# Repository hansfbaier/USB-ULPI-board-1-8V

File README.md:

USB ULPI high speed PHY with 1.8V IO voltage
and Waveshare USB3300 board pinout
===

[![CC BY-SA 4.0][cc-by-sa-shield]][cc-by-sa]

This work is licensed under a [Creative Commons Attribution-NonCommercial-ShareAlike 4.0 International License][cc-by-sa].

[![CC BY-SA 4.0][cc-by-sa-image]][cc-by-sa]

[cc-by-sa]: http://creativecommons.org/licenses/by-nc-sa/4.0/
[cc-by-sa-image]: https://licensebuttons.net/l/by-nc-sa/4.0/88x31.png
[cc-by-sa-shield]: https://img.shields.io/badge/License-CC%20BY--NC--SA%204.0-lightgrey.svg

## Images

### JLCPCB

PCBs can be ordered fully-assembled (besides the pin header) from [JLCPCB](https://jlcpcb.com). Required files are
[PmodUsbUlpi_cpl_jlc.csv](PmodUsbUlpi_cpl_jlc.csv), [PmodUsbUlpi_bom_jlc.csv](PmodUsbUlpi_cpl_jlc.csv) and
[Gerber/PmodUsbUlpi.zip](Gerber/UsbUlpi.zip).

## Status
I am not sure the board works yet. I could not get it working on a couple of boards.
The 3.3V Version it is also very board dependent, on some boards it would work,
on others not, but I didn't test as many yet as with the 3.3V version.

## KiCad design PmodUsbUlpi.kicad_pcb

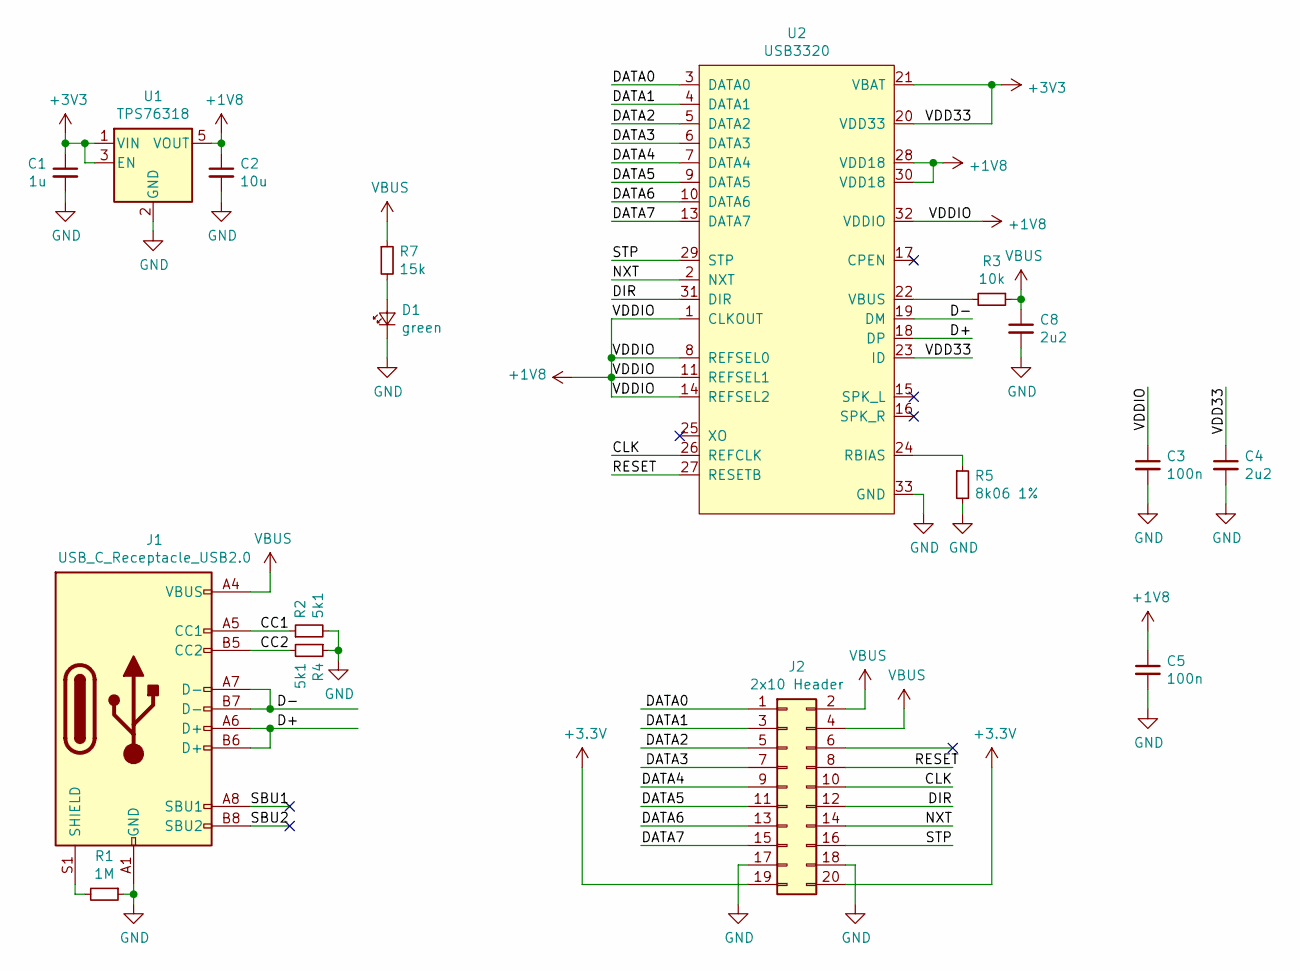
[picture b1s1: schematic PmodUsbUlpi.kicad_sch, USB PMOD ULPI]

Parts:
C1: 1u; C_0603_1608Metric; LCSC C15849
C2: 10u; C_0603_1608Metric; LCSC C19702
C3, C5: 100n; C_0603_1608Metric; LCSC C14663
C4, C8: 2u2; C_0603_1608Metric; LCSC C23630
D1: green; LED_0603_1608Metric; LCSC C72043
J1: USB_C_Receptacle_USB2.0; USB_C_Receptacle_XKB_U262-16XN-4BVC11; LCSC C165948
J2: 2x10 Header; PinHeader_2x10_P2.54mm_Horizontal
R1: 1M; R_0603_1608Metric; LCSC C22935
R2, R4: 5k1; R_0603_1608Metric; LCSC C23186
R3: 10k; R_0603_1608Metric; LCSC C25804
R5: 8k06 1%; R_0603_1608Metric; LCSC C23112
R7: 15k; R_0603_1608Metric; LCSC C22809
U1: TPS76318; SOT-23-5; LCSC C7099
U2: USB3320; QFN-32-1EP_5x5mm_P0.5mm_EP3.3x3.3mm; LCSC C132156

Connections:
+1V8: C2.1, C3.1, C5.1, U1.5 (VOUT), U2.1 (CLKOUT), U2.8 (REFSEL0), U2.11 (REFSEL1), U2.14 (REFSEL2), U2.28 (VDD18), U2.30 (VDD18), U2.32 (VDDIO)
/CC1: J1.A5 (CC1), R2.1
/CC2: J1.B5 (CC2), R4.2
/CLK: J2.10, U2.26 (REFCLK)
/D+: J1.A6 (D+), J1.B6 (D+), U2.18 (DP)
/D-: J1.A7 (D-), J1.B7 (D-), U2.19 (DM)
/DATA0: J2.1, U2.3 (DATA0)
/DATA1: J2.3, U2.4 (DATA1)
/DATA2: J2.5, U2.5 (DATA2)
/DATA3: J2.7, U2.6 (DATA3)
/DATA4: J2.9, U2.7 (DATA4)
/DATA5: J2.11, U2.9 (DATA5)
/DATA6: J2.13, U2.10 (DATA6)
/DATA7: J2.15, U2.13 (DATA7)
/DIR: J2.12, U2.31 (DIR)
/NXT: J2.14, U2.2 (NXT)
/RESET: J2.8, U2.27 (RESETB)
/SBU1: J1.A8 (SBU1)
/SBU2: J1.B8 (SBU2)
/STP: J2.16, U2.29 (STP)
GND: C1.2, C2.2, C3.2, C4.2, C5.2, C8.2, D1.1 (K), J1.A1 (GND), J1.A12 (GND), J1.B1 (GND), J1.B12 (GND), J2.17, J2.18, R1.1, R2.2, R4.1, R5.2, U1.2 (GND), U2.33 (GND)
unnamed: D1.2 (A), R7.2
unnamed: J1.S1 (SHIELD), R1.2
unnamed: R3.2, U2.22 (VBUS)
unnamed: R5.1, U2.24 (RBIAS)
VBUS: C8.1, J1.A4 (VBUS), J1.A9 (VBUS), J1.B4 (VBUS), J1.B9 (VBUS), J2.2, J2.4, R3.1, R7.1

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
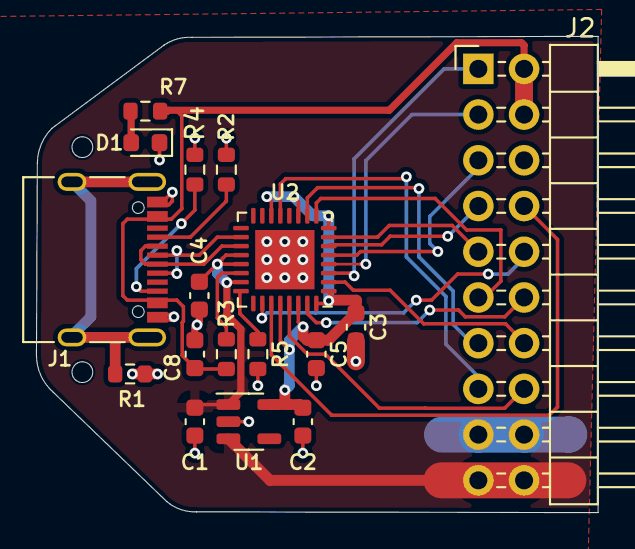
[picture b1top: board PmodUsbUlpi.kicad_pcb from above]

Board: 2 copper layers, 31.2 x 26.5 mm, 18 parts (1 on the bottom side), 25 nets.

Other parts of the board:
REFm**: KiCad-Logo2_5mm_SilkScreen

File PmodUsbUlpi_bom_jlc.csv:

Comment,Designator,Footprint,LCSC
"1u","C1","Capacitor_SMD:C_0603_1608Metric","C15849"
"10u","C2","Capacitor_SMD:C_0603_1608Metric","C19702"
"100n","C3,C5","Capacitor_SMD:C_0603_1608Metric","C14663"
"2u2","C4,C8","Capacitor_SMD:C_0603_1608Metric","C23630"
"green","D1","LED_SMD:LED_0603_1608Metric","C72043"
"USB_C_Receptacle_USB2.0","J1","Connector_USB:USB_C_Receptacle_XKB_U262-16XN-4BVC11","C165948"
"2x10 Header","J2","Connector_PinHeader_2.54mm:PinHeader_2x10_P2.54mm_Horizontal",""
"1M","R1","Resistor_SMD:R_0603_1608Metric","C22935"
"5k1","R2,R4","Resistor_SMD:R_0603_1608Metric","C23186"
"10k","R3","Resistor_SMD:R_0603_1608Metric","C25804"
"8k06 1%","R5","Resistor_SMD:R_0603_1608Metric","C23112"
"15k","R7","Resistor_SMD:R_0603_1608Metric","C22809"
"TPS76318","U1","Package_TO_SOT_SMD:SOT-23-5","C7099"
"USB3320","U2","Package_DFN_QFN:QFN-32-1EP_5x5mm_P0.5mm_EP3.3x3.3mm","C132156"

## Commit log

2021-06-29 First Version with Waveshare Pinout
2021-06-29 first version with 1.8V
2021-06-29 change image
2021-06-29 Tweak a couple of traces (better crossings)
2021-06-29 fix PCB image version
2021-06-29 update production files
2021-06-29 Update Gerber ZIP file and README
2021-06-30 add rendered images

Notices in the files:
PmodUsbUlpi.kicad_pcb:
License: CC-BY-SA 4.0
